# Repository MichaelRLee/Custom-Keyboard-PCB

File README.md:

# Lee Keyboard PCBs

Open source, hot-swappable board PCBs designed to be controlled by commonly available microcontroller boards (Pro Micro for the numpad, and Teensy LC, 3.2, etc. for the TKL).  These could easily be swapped out for any other board, but the qmk firmware would need to be modified for the specific controller.

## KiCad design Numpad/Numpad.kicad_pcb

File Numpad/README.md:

# leepad

<table>
<th colspan=2 style="text-align:center">Firmware</th>
<tr>
<td><a href="https://github.com/MichaelRLee/qmk_firmware/tree/numpad/keyboards/finz/leepad">QMK</a></td>
<td><a href="https://github.com/MichaelRLee/vial-qmk/tree/numpad/keyboards/finz/leepad">Vial</a></td>
</tr>
</table>

A hotswappable numpad with extra macro keys.  Designed with the intention of using a Pro Micro as the controller, though the the spacing between the two PTH collumns do not reflect this.  What that means is that wires will have to be used in place of at least one row of pin headers.  The rational for this is to allow flexibility when mounting the Pro Micro (left or right side, or relocate the Pro Micro entirely).

Files (kicad and gerber) for a mounting plate are also included, which can easily be manufactured at the same time as the PCB.  For reference, the spacing between the macro keys and the rest of the keybaord is 0.25u, and all stabalizers have the wires facing inwards.

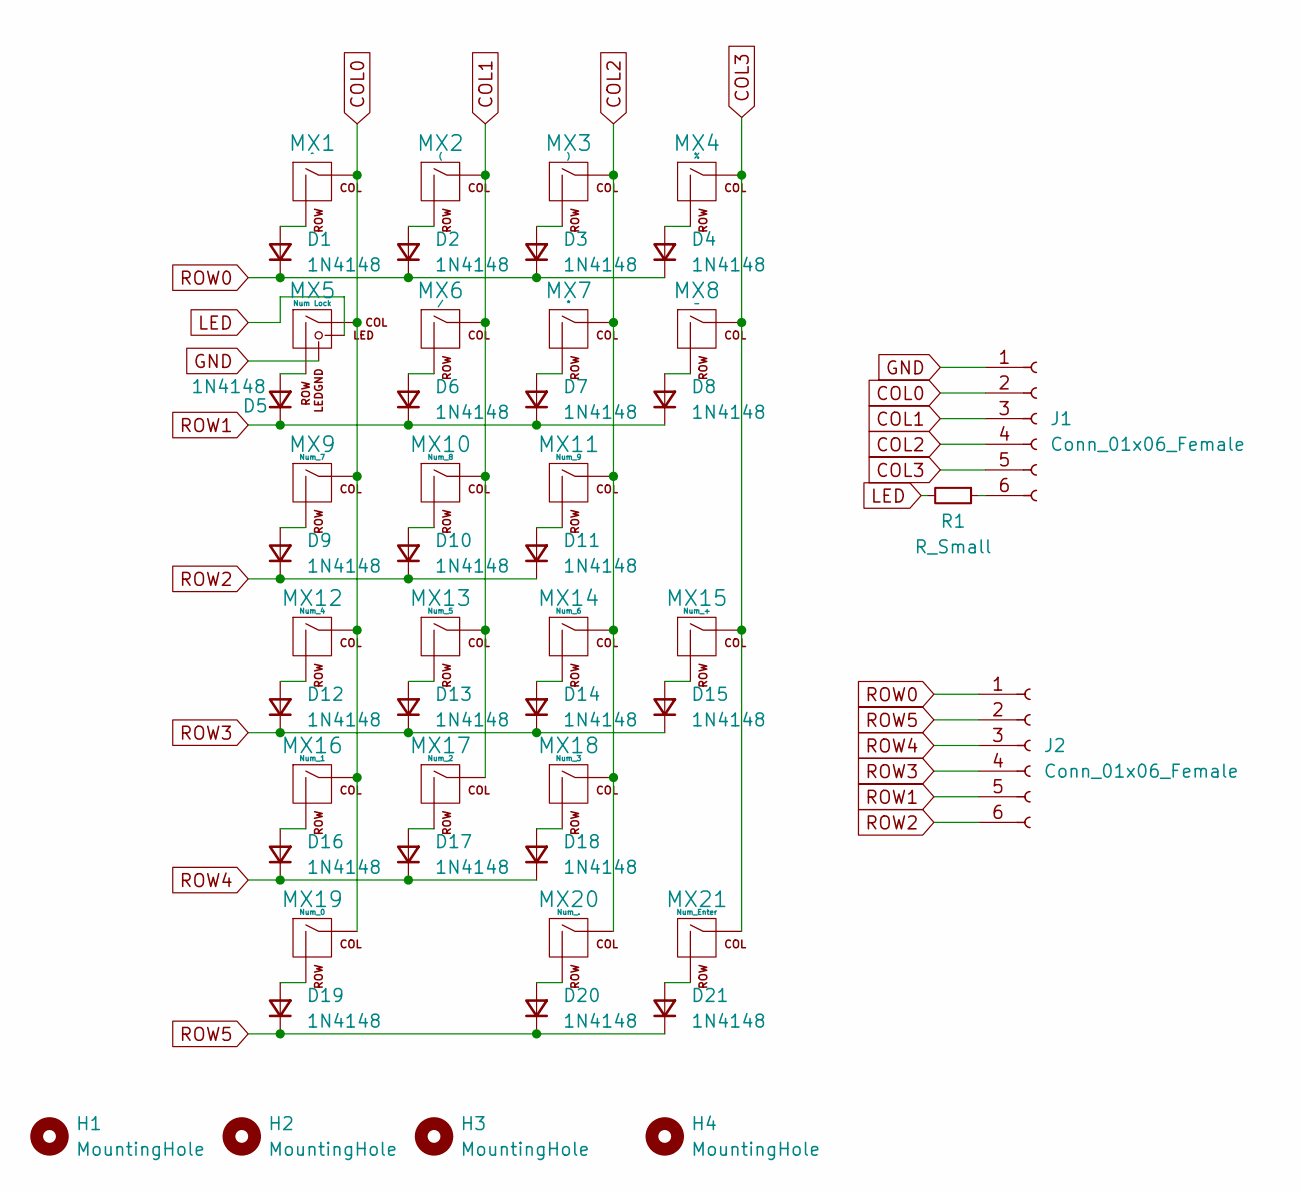
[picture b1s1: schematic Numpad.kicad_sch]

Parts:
D1, D2, D3, D4, D5, D6, D7, D8, D9, D10, D11, D12, D13, D14, D15, D16, D17, D18, D19, D20, D21: 1N4148; D_DO-34_SOD68_P7.62mm_Horizontal
H1, H2, H3, H4: MountingHole; MountingHole_2.2mm_M2_Pad
J1, J2: Conn_01x06_Female; PinHeader_1x06_P2.54mm_Vertical
MX1: ^; MXOnly-1U-Hotswap-Antishear
MX2: (; MXOnly-1U-Hotswap-Antishear
MX3: ); MXOnly-1U-Hotswap-Antishear
MX4: %; MXOnly-1U-Hotswap-Antishear
MX5: Num Lock; MXOnly-1U-Hotswap-Antishear-LED
MX6: /; MXOnly-1U-Hotswap-Antishear
MX7: *; MXOnly-1U-Hotswap-Antishear
MX8: -; MXOnly-1U-Hotswap-Antishear
MX9: Num_7; MXOnly-1U-Hotswap-Antishear
MX10: Num_8; MXOnly-1U-Hotswap-Antishear
MX11: Num_9; MXOnly-1U-Hotswap-Antishear
MX12: Num_4; MXOnly-1U-Hotswap-Antishear
MX13: Num_5; MXOnly-1U-Hotswap-Antishear
MX14: Num_6; MXOnly-1U-Hotswap-Antishear
MX15: Num_+; MXOnly-2U-Hotswap-Antishear-ReversedVerticalStabilizers
MX16: Num_1; MXOnly-1U-Hotswap-Antishear
MX17: Num_2; MXOnly-1U-Hotswap-Antishear
MX18: Num_3; MXOnly-1U-Hotswap-Antishear
MX19: Num_0; MXOnly-2U-Hotswap-Antishear-ReversedStabilizers
MX20: Num_.; MXOnly-1U-Hotswap-Antishear
MX21: Num_Enter; MXOnly-2U-Hotswap-Antishear-ReversedVerticalStabilizers
R1: R_Small; R_Axial_DIN0207_L6.3mm_D2.5mm_P10.16mm_Horizontal

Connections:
COL0: J1.2, MX1.1 (COL), MX5.1 (COL), MX9.1 (COL), MX12.1 (COL), MX16.1 (COL), MX19.1 (COL)
COL1: J1.3, MX2.1 (COL), MX6.1 (COL), MX10.1 (COL), MX13.1 (COL), MX17.1 (COL)
COL2: J1.4, MX3.1 (COL), MX7.1 (COL), MX11.1 (COL), MX14.1 (COL), MX18.1 (COL), MX20.1 (COL)
COL3: J1.5, MX4.1 (COL), MX8.1 (COL), MX15.1 (COL), MX21.1 (COL)
GND: J1.1, MX5.4 (LEDGND)
LED: MX5.3 (LED), R1.2
unnamed: D1.2 (A), MX1.2 (ROW)
unnamed: D2.2 (A), MX2.2 (ROW)
unnamed: D3.2 (A), MX3.2 (ROW)
unnamed: D4.2 (A), MX4.2 (ROW)
unnamed: D5.2 (A), MX5.2 (ROW)
unnamed: D6.2 (A), MX6.2 (ROW)
unnamed: D7.2 (A), MX7.2 (ROW)
unnamed: D8.2 (A), MX8.2 (ROW)
unnamed: D9.2 (A), MX9.2 (ROW)
unnamed: D10.2 (A), MX10.2 (ROW)
unnamed: D11.2 (A), MX11.2 (ROW)
unnamed: D12.2 (A), MX12.2 (ROW)
unnamed: D13.2 (A), MX13.2 (ROW)
unnamed: D14.2 (A), MX14.2 (ROW)
unnamed: D15.2 (A), MX15.2 (ROW)
unnamed: D16.2 (A), MX16.2 (ROW)
unnamed: D17.2 (A), MX17.2 (ROW)
unnamed: D18.2 (A), MX18.2 (ROW)
unnamed: D19.2 (A), MX19.2 (ROW)
unnamed: D20.2 (A), MX20.2 (ROW)
unnamed: D21.2 (A), MX21.2 (ROW)
unnamed: J1.6, R1.1
ROW0: D1.1 (K), D2.1 (K), D3.1 (K), D4.1 (K), J2.1
ROW1: D5.1 (K), D6.1 (K), D7.1 (K), D8.1 (K), J2.5
ROW2: D9.1 (K), D10.1 (K), D11.1 (K), J2.6
ROW3: D12.1 (K), D13.1 (K), D14.1 (K), D15.1 (K), J2.4
ROW4: D16.1 (K), D17.1 (K), D18.1 (K), J2.3
ROW5: D19.1 (K), D20.1 (K), D21.1 (K), J2.2

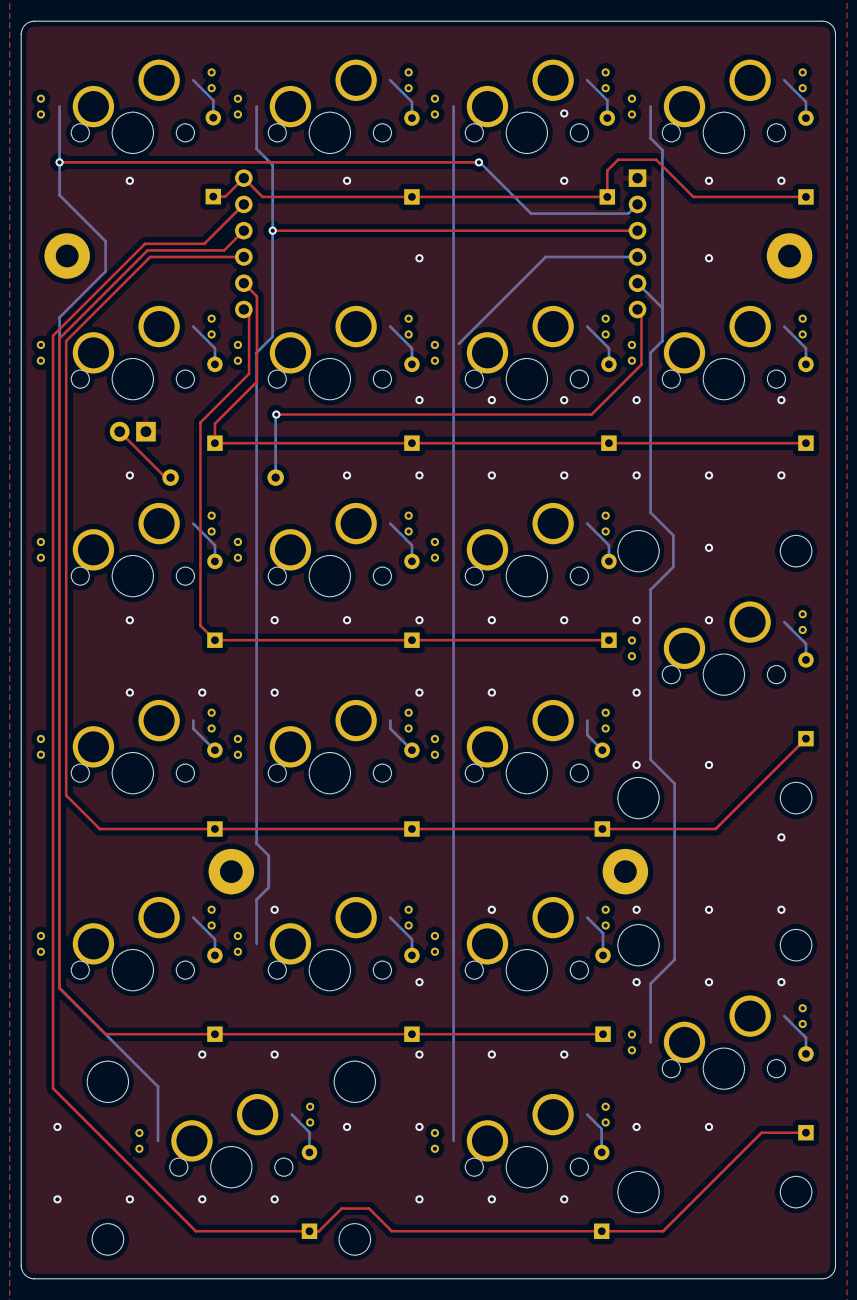
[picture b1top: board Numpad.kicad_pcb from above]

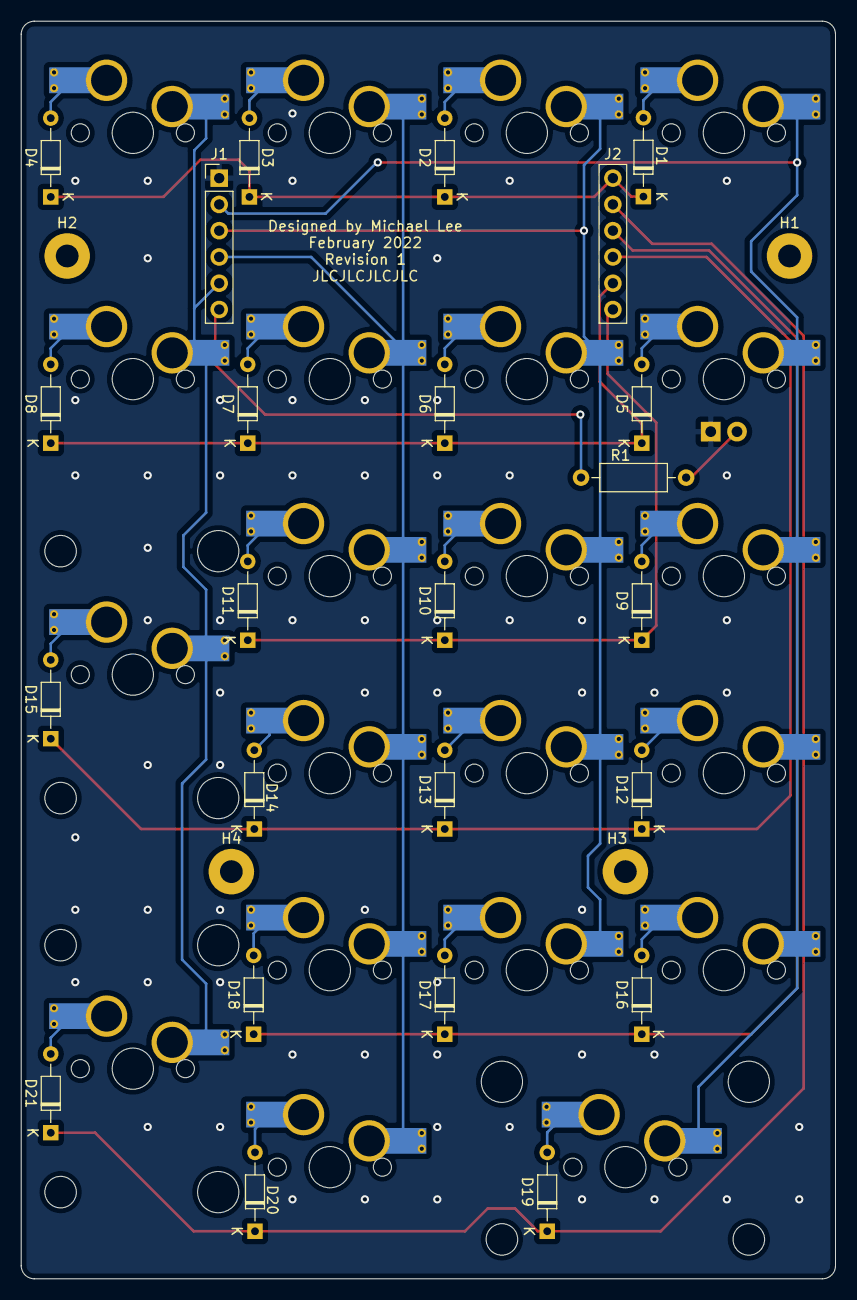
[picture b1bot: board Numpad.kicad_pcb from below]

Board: 2 copper layers, 78.7 x 121.6 mm, 49 parts (28 on the bottom side), 34 nets.

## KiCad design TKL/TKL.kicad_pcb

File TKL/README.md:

# tenleeless

<table>
<th colspan=2 style="text-align:center">Firmware</th>
<tr>
<td><a href="https://github.com/MichaelRLee/qmk_firmware/tree/tenkeyless/keyboards/finz/tenleeless">QMK</a></td>
<td><a href="">Vial</a></td>
</tr>
</table>

A hotswappable tenkeyless board, designed  with using a Teensy 3.2 as the controller.  Other controller boards with the same pinout (like the Teensy LC), should be usable, or any board with enough pins if not using pin headers (though adjustments to the QMK firmware would be needed).

### Design notes

The gap between the function keys and the alphanumeric cluster, as well as between the cluster and the nav keys, is 0.25u.  The spacebar stabalizer is the only one that has been flipped (wire north of the switch).  Any non-tray mounted mounting plate that fits the above should work with this PCB, though it was designed using a kbd8x plate as reference.

The board was is limted to a 7u space bar (1.5u ctrl/alt keys and 1u win keys, no fn/menu key), as well as a stepped caps lock.

As the microcontroller is located above the left arrow key, you may want to use a daughterboard (or female USB port).

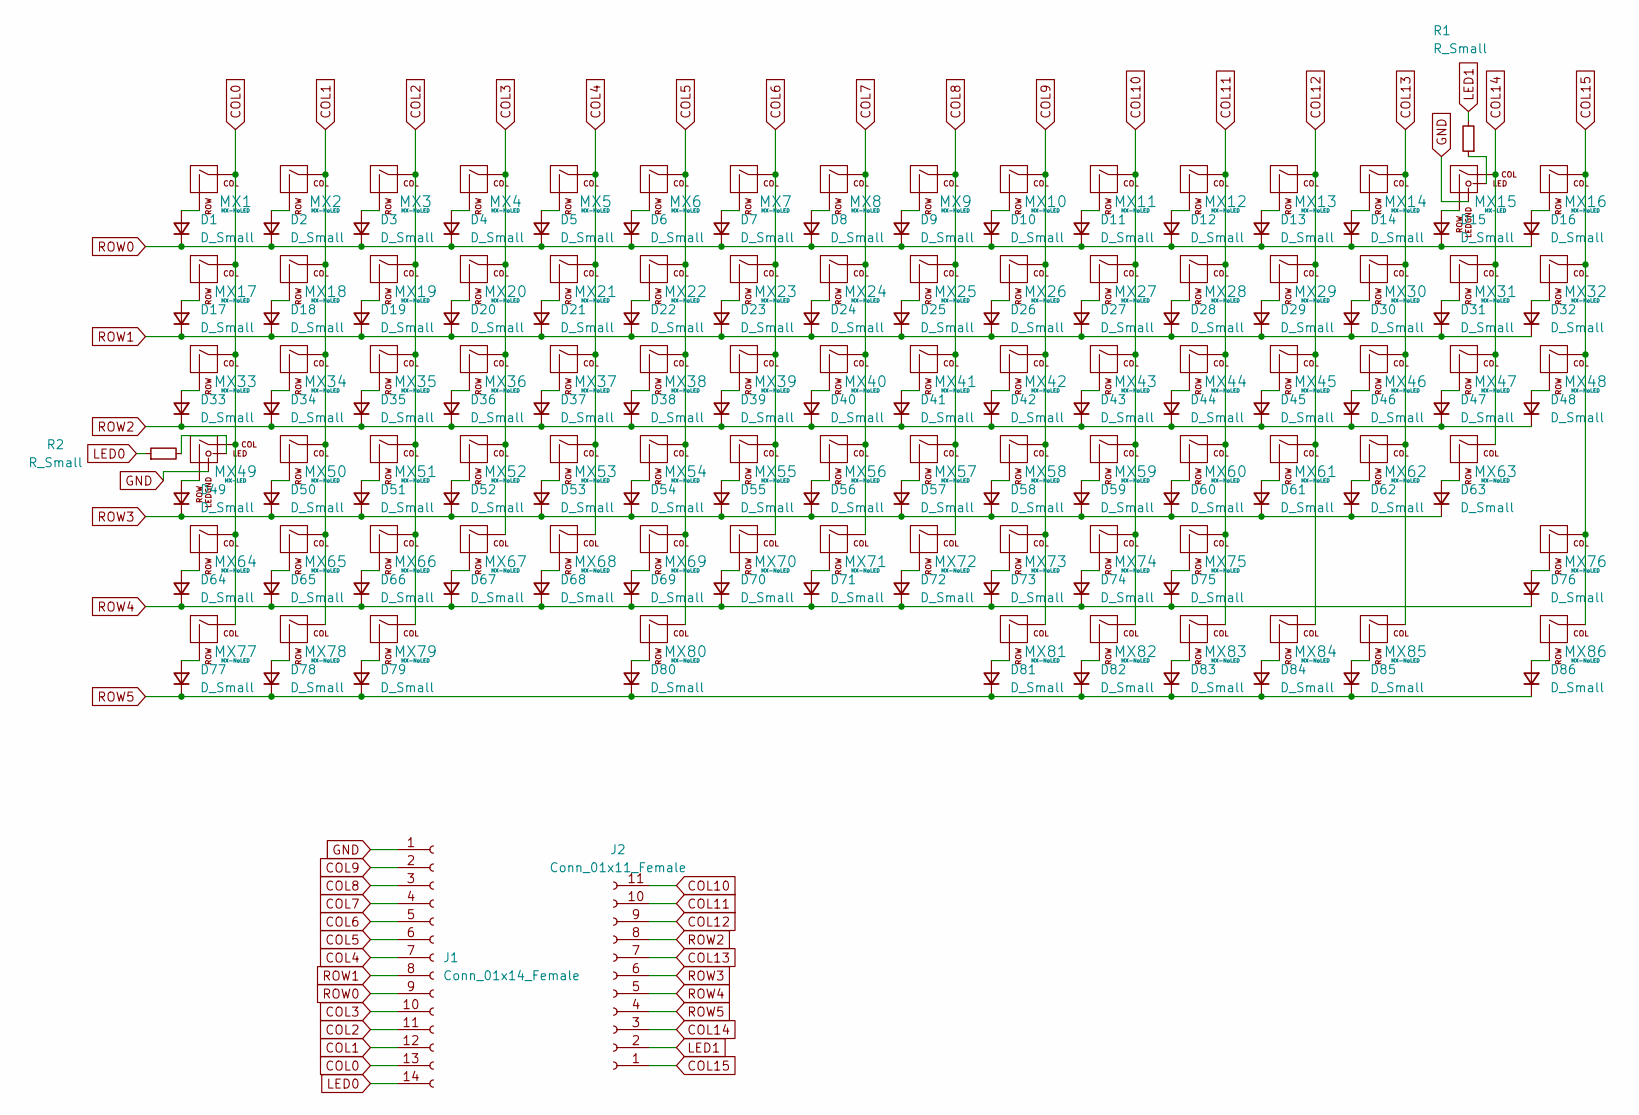
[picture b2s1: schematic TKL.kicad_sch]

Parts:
D1, D2, D3, D4, D5, D6, D7, D8, D9, D10, D11, D12, D13, D14, D15, D16, D17, D18, D19, D20, D21, D22, D23, D24, D25, D26, D27, D28, D29, D30, D31, D32, D33, D34, D35, D36, D37, D38, D39, D40, D41, D42, D43, D44, D45, D46, D47, D48, D49, D50, D51, D52, D53, D54, D55, D56, D57, D58, D59, D60, D61, D62, D63, D64, D65, D66, D67, D68, D69, D70, D71, D72, D73, D74, D75, D76, D77, D78, D79, D80, D81, D82, D83, D84, D85, D86: D_Small; D_DO-35_SOD27_P7.62mm_Horizontal
J1: Conn_01x14_Female; PinHeader_1x14_P2.54mm_Vertical
J2: Conn_01x11_Female; PinHeader_1x11_P2.54mm_Vertical
MX1, MX2, MX3, MX4, MX5, MX6, MX7, MX8, MX9, MX10, MX11, MX12, MX13, MX14, MX16, MX18, MX19, MX20, MX21, MX22, MX23, MX24, MX25, MX26, MX27, MX28, MX29, MX31, MX32, MX34, MX35, MX36, MX37, MX38, MX39, MX40, MX41, MX42, MX43, MX44, MX45, MX47, MX48, MX50, MX51, MX52, MX53, MX54, MX55, MX56, MX57, MX58, MX59, MX60, MX62, MX63, MX65, MX66, MX67, MX68, MX69, MX70, MX71, MX72, MX73, MX74, MX76, MX78, MX82, MX84, MX85, MX86: MX-NoLED; MXOnly-1U-Hotswap-Antishear
MX15: MX-LED; MXOnly-1U-Hotswap-Antishear-LED
MX17: MX-NoLED; MXOnly-1U-Hotswap
MX30: MX-NoLED; MXOnly-2U-Hotswap-Antishear
MX33, MX46, MX77, MX79, MX81, MX83: MX-NoLED; MXOnly-1.5U-Hotswap-Antishear
MX49: MX-LED; MXOnly-Caps-Hotswap-Antishear-LED
MX61, MX64: MX-NoLED; MXOnly-2.25U-Hotswap-Antishear
MX75: MX-NoLED; MXOnly-2.75U-Hotswap-Antishear
MX80: MX-NoLED; MXOnly-7U-Hotswap-Antishear
R1, R2: R_Small; R_Axial_DIN0207_L6.3mm_D2.5mm_P7.62mm_Horizontal

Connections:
COL0: J1.13, MX1.1 (COL), MX17.1 (COL), MX33.1 (COL), MX49.1 (COL), MX64.1 (COL), MX77.1 (COL)
COL1: J1.12, MX2.1 (COL), MX18.1 (COL), MX34.1 (COL), MX50.1 (COL), MX65.1 (COL), MX78.1 (COL)
COL2: J1.11, MX3.1 (COL), MX19.1 (COL), MX35.1 (COL), MX51.1 (COL), MX66.1 (COL), MX79.1 (COL)
COL3: J1.10, MX4.1 (COL), MX20.1 (COL), MX36.1 (COL), MX52.1 (COL), MX67.1 (COL)
COL4: J1.7, MX5.1 (COL), MX21.1 (COL), MX37.1 (COL), MX53.1 (COL), MX68.1 (COL)
COL5: J1.6, MX6.1 (COL), MX22.1 (COL), MX38.1 (COL), MX54.1 (COL), MX69.1 (COL), MX80.1 (COL)
COL6: J1.5, MX7.1 (COL), MX23.1 (COL), MX39.1 (COL), MX55.1 (COL), MX70.1 (COL)
COL7: J1.4, MX8.1 (COL), MX24.1 (COL), MX40.1 (COL), MX56.1 (COL), MX71.1 (COL)
COL8: J1.3, MX9.1 (COL), MX25.1 (COL), MX41.1 (COL), MX57.1 (COL), MX72.1 (COL)
COL9: J1.2, MX10.1 (COL), MX26.1 (COL), MX42.1 (COL), MX58.1 (COL), MX73.1 (COL), MX81.1 (COL)
COL10: J2.11, MX11.1 (COL), MX27.1 (COL), MX43.1 (COL), MX59.1 (COL), MX74.1 (COL), MX82.1 (COL)
COL11: J2.10, MX12.1 (COL), MX28.1 (COL), MX44.1 (COL), MX60.1 (COL), MX75.1 (COL), MX83.1 (COL)
COL12: J2.9, MX13.1 (COL), MX29.1 (COL), MX45.1 (COL), MX61.1 (COL), MX84.1 (COL)
COL13: J2.7, MX14.1 (COL), MX30.1 (COL), MX46.1 (COL), MX62.1 (COL), MX85.1 (COL)
COL14: J2.3, MX15.1 (COL), MX31.1 (COL), MX47.1 (COL), MX63.1 (COL)
COL15: J2.1, MX16.1 (COL), MX32.1 (COL), MX48.1 (COL), MX76.1 (COL), MX86.1 (COL)
GND: J1.1, MX15.4 (LEDGND), MX49.4 (LEDGND)
LED0: J1.14, R2.1
LED1: J2.2, R1.2
unnamed: D1.2 (A), MX1.2 (ROW)
unnamed: D2.2 (A), MX2.2 (ROW)
unnamed: D3.2 (A), MX3.2 (ROW)
unnamed: D4.2 (A), MX4.2 (ROW)
unnamed: D5.2 (A), MX5.2 (ROW)
unnamed: D6.2 (A), MX6.2 (ROW)
unnamed: D7.2 (A), MX7.2 (ROW)
unnamed: D8.2 (A), MX8.2 (ROW)
unnamed: D9.2 (A), MX9.2 (ROW)
unnamed: D10.2 (A), MX10.2 (ROW)
unnamed: D11.2 (A), MX11.2 (ROW)
unnamed: D12.2 (A), MX12.2 (ROW)
unnamed: D13.2 (A), MX13.2 (ROW)
unnamed: D14.2 (A), MX14.2 (ROW)
unnamed: D15.2 (A), MX15.2 (ROW)
unnamed: D16.2 (A), MX16.2 (ROW)
unnamed: D17.2 (A), MX17.2 (ROW)
unnamed: D18.2 (A), MX18.2 (ROW)
unnamed: D19.2 (A), MX19.2 (ROW)
unnamed: D20.2 (A), MX20.2 (ROW)
unnamed: D21.2 (A), MX21.2 (ROW)
unnamed: D22.2 (A), MX22.2 (ROW)
unnamed: D23.2 (A), MX23.2 (ROW)
unnamed: D24.2 (A), MX24.2 (ROW)
unnamed: D25.2 (A), MX25.2 (ROW)
unnamed: D26.2 (A), MX26.2 (ROW)
unnamed: D27.2 (A), MX27.2 (ROW)
unnamed: D28.2 (A), MX28.2 (ROW)
unnamed: D29.2 (A), MX29.2 (ROW)
unnamed: D30.2 (A), MX30.2 (ROW)
unnamed: D31.2 (A), MX31.2 (ROW)
unnamed: D32.2 (A), MX32.2 (ROW)
unnamed: D33.2 (A), MX33.2 (ROW)
unnamed: D34.2 (A), MX34.2 (ROW)
unnamed: D35.2 (A), MX35.2 (ROW)
unnamed: D36.2 (A), MX36.2 (ROW)
unnamed: D37.2 (A), MX37.2 (ROW)
unnamed: D38.2 (A), MX38.2 (ROW)
unnamed: D39.2 (A), MX39.2 (ROW)
unnamed: D40.2 (A), MX40.2 (ROW)
unnamed: D41.2 (A), MX41.2 (ROW)
unnamed: D42.2 (A), MX42.2 (ROW)
unnamed: D43.2 (A), MX43.2 (ROW)
unnamed: D44.2 (A), MX44.2 (ROW)
unnamed: D45.2 (A), MX45.2 (ROW)
unnamed: D46.2 (A), MX46.2 (ROW)
unnamed: D47.2 (A), MX47.2 (ROW)
unnamed: D48.2 (A), MX48.2 (ROW)
unnamed: D49.2 (A), MX49.2 (ROW)
unnamed: D50.2 (A), MX50.2 (ROW)
unnamed: D51.2 (A), MX51.2 (ROW)
unnamed: D52.2 (A), MX52.2 (ROW)
unnamed: D53.2 (A), MX53.2 (ROW)
unnamed: D54.2 (A), MX54.2 (ROW)
unnamed: D55.2 (A), MX55.2 (ROW)
unnamed: D56.2 (A), MX56.2 (ROW)
unnamed: D57.2 (A), MX57.2 (ROW)
unnamed: D58.2 (A), MX58.2 (ROW)
unnamed: D59.2 (A), MX59.2 (ROW)
unnamed: D60.2 (A), MX60.2 (ROW)
unnamed: D61.2 (A), MX61.2 (ROW)
unnamed: D62.2 (A), MX62.2 (ROW)
unnamed: D63.2 (A), MX63.2 (ROW)
unnamed: D64.2 (A), MX64.2 (ROW)
unnamed: D65.2 (A), MX65.2 (ROW)
unnamed: D66.2 (A), MX66.2 (ROW)
unnamed: D67.2 (A), MX67.2 (ROW)
unnamed: D68.2 (A), MX68.2 (ROW)
unnamed: D69.2 (A), MX69.2 (ROW)
unnamed: D70.2 (A), MX70.2 (ROW)
unnamed: D71.2 (A), MX71.2 (ROW)
unnamed: D72.2 (A), MX72.2 (ROW)
unnamed: D73.2 (A), MX73.2 (ROW)
unnamed: D74.2 (A), MX74.2 (ROW)
unnamed: D75.2 (A), MX75.2 (ROW)
unnamed: D76.2 (A), MX76.2 (ROW)
unnamed: D77.2 (A), MX77.2 (ROW)
unnamed: D78.2 (A), MX78.2 (ROW)
unnamed: D79.2 (A), MX79.2 (ROW)
unnamed: D80.2 (A), MX80.2 (ROW)
unnamed: D81.2 (A), MX81.2 (ROW)
unnamed: D82.2 (A), MX82.2 (ROW)
unnamed: D83.2 (A), MX83.2 (ROW)
unnamed: D84.2 (A), MX84.2 (ROW)
unnamed: D85.2 (A), MX85.2 (ROW)
unnamed: D86.2 (A), MX86.2 (ROW)
unnamed: MX15.3 (LED), R1.1
unnamed: MX49.3 (LED), R2.2
ROW0: D1.1 (K), D2.1 (K), D3.1 (K), D4.1 (K), D5.1 (K), D6.1 (K), D7.1 (K), D8.1 (K), D9.1 (K), D10.1 (K), D11.1 (K), D12.1 (K), D13.1 (K), D14.1 (K), D15.1 (K), D16.1 (K), J1.9
ROW1: D17.1 (K), D18.1 (K), D19.1 (K), D20.1 (K), D21.1 (K), D22.1 (K), D23.1 (K), D24.1 (K), D25.1 (K), D26.1 (K), D27.1 (K), D28.1 (K), D29.1 (K), D30.1 (K), D31.1 (K), D32.1 (K), J1.8
ROW2: D33.1 (K), D34.1 (K), D35.1 (K), D36.1 (K), D37.1 (K), D38.1 (K), D39.1 (K), D40.1 (K), D41.1 (K), D42.1 (K), D43.1 (K), D44.1 (K), D45.1 (K), D46.1 (K), D47.1 (K), D48.1 (K), J2.8
ROW3: D49.1 (K), D50.1 (K), D51.1 (K), D52.1 (K), D53.1 (K), D54.1 (K), D55.1 (K), D56.1 (K), D57.1 (K), D58.1 (K), D59.1 (K), D60.1 (K), D61.1 (K), D62.1 (K), D63.1 (K), J2.6
ROW4: D64.1 (K), D65.1 (K), D66.1 (K), D67.1 (K), D68.1 (K), D69.1 (K), D70.1 (K), D71.1 (K), D72.1 (K), D73.1 (K), D74.1 (K), D75.1 (K), D76.1 (K), J2.5
ROW5: D77.1 (K), D78.1 (K), D79.1 (K), D80.1 (K), D81.1 (K), D82.1 (K), D83.1 (K), D84.1 (K), D85.1 (K), D86.1 (K), J2.4

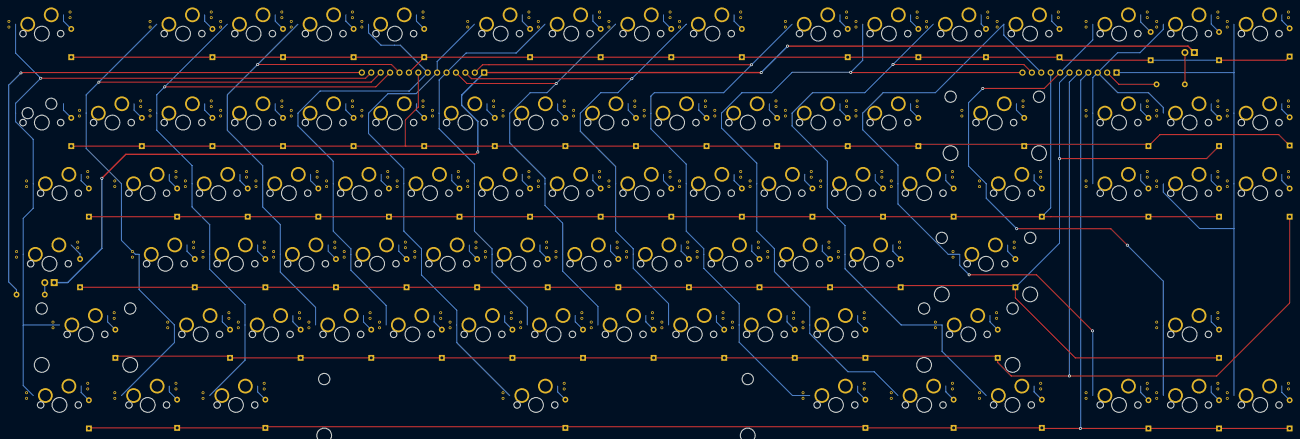
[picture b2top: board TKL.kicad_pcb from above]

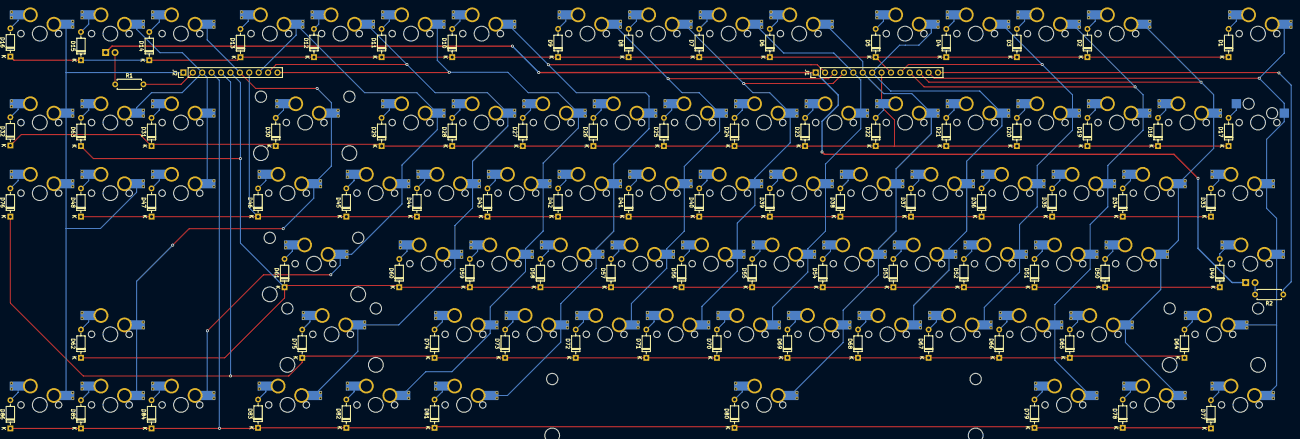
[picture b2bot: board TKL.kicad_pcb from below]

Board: 2 copper layers, 176 parts (90 on the bottom side), 113 nets.

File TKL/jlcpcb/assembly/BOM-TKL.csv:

Comment,Designator,Footprint,LCSC
Tab,MX33,MXOnly-1.5U-Hotswap-Antishear,
;,MX59,MXOnly-1U-Hotswap-Antishear,
R_Alt,MX81,MXOnly-1.5U-Hotswap-Antishear,
v,MX68,MXOnly-1U-Hotswap-Antishear,
Insert,MX31,MXOnly-1U-Hotswap-Antishear,
m,MX71,MXOnly-1U-Hotswap-Antishear,
F10,MX11,MXOnly-1U-Hotswap-Antishear,
Page Down,MX76,MXOnly-1U-Hotswap-Antishear,
F5,MX6,MXOnly-1U-Hotswap-Antishear,
Enter,MX61,MXOnly-2.25U-Hotswap-Antishear,
r,MX37,MXOnly-1U-Hotswap-Antishear,
x,MX66,MXOnly-1U-Hotswap-Antishear,
",",MX72,MXOnly-1U-Hotswap-Antishear,
L_Alt,MX79,MXOnly-1.5U-Hotswap-Antishear,
9,MX26,MXOnly-1U-Hotswap-Antishear,
5,MX22,MXOnly-1U-Hotswap-Antishear,
L_Shift,MX64,MXOnly-2.25U-Hotswap-Antishear,
-,MX28,MXOnly-1U-Hotswap-Antishear,
0,MX27,MXOnly-1U-Hotswap-Antishear,
=,MX29,MXOnly-1U-Hotswap-Antishear,
z,MX65,MXOnly-1U-Hotswap-Antishear,
g,MX54,MXOnly-1U-Hotswap-Antishear,
o,MX42,MXOnly-1U-Hotswap-Antishear,
Pause,MX16,MXOnly-1U-Hotswap-Antishear,
F4,MX5,MXOnly-1U-Hotswap-Antishear,
7,MX24,MXOnly-1U-Hotswap-Antishear,
j,MX56,MXOnly-1U-Hotswap-Antishear,
F11,MX12,MXOnly-1U-Hotswap-Antishear,
Backspace,MX30,MXOnly-2U-Hotswap-Antishear,
h,MX55,MXOnly-1U-Hotswap-Antishear,
.,MX73,MXOnly-1U-Hotswap-Antishear,
End,MX48,MXOnly-1U-Hotswap-Antishear,
Print Screen,MX14,MXOnly-1U-Hotswap-Antishear,
q,MX34,MXOnly-1U-Hotswap-Antishear,
3,MX20,MXOnly-1U-Hotswap-Antishear,
p,MX43,MXOnly-1U-Hotswap-Antishear,
c,MX67,MXOnly-1U-Hotswap-Antishear,
n,MX70,MXOnly-1U-Hotswap-Antishear,
F8,MX9,MXOnly-1U-Hotswap-Antishear,
],MX45,MXOnly-1U-Hotswap-Antishear,
Page Up,MX32,MXOnly-1U-Hotswap-Antishear,
y,MX39,MXOnly-1U-Hotswap-Antishear,
F2,MX3,MXOnly-1U-Hotswap-Antishear,
i,MX41,MXOnly-1U-Hotswap-Antishear,
a,MX50,MXOnly-1U-Hotswap-Antishear,
F1,MX2,MXOnly-1U-Hotswap-Antishear,
\,MX46,MXOnly-1.5U-Hotswap-Antishear,
Teensy3.2,U1,Teensy30_31_32_LC,
L_Ctrl,MX77,MXOnly-1.5U-Hotswap-Antishear,
2,MX19,MXOnly-1U-Hotswap-Antishear,
L_Win,MX78,MXOnly-1U-Hotswap-Antishear,
Scroll Lock,MX15,MXOnly-1U-Hotswap-Antishear-LED,
[,MX44,MXOnly-1U-Hotswap-Antishear,
R_Shift,MX75,MXOnly-2.75U-Hotswap-Antishear,
Down,MX85,MXOnly-1U-Hotswap-Antishear,
F6,MX7,MXOnly-1U-Hotswap-Antishear,
',MX60,MXOnly-1U-Hotswap-Antishear,
u,MX40,MXOnly-1U-Hotswap-Antishear,
Left,MX84,MXOnly-1U-Hotswap-Antishear,
4,MX21,MXOnly-1U-Hotswap-Antishear,
Space,MX80,MXOnly-7U-Hotswap-Antishear-ReversedStabilizers,
Caps Lock,MX49,MXOnly-1U-Hotswap-Antishear-LED,
F3,MX4,MXOnly-1U-Hotswap-Antishear,
Esc,MX1,MXOnly-1U-Hotswap-Antishear,
6,MX23,MXOnly-1U-Hotswap-Antishear,
F12,MX13,MXOnly-1U-Hotswap-Antishear,
t,MX38,MXOnly-1U-Hotswap-Antishear,
Home,MX63,MXOnly-1U-Hotswap-Antishear,
R_Ctrl,MX83,MXOnly-1.5U-Hotswap-Antishear,
F7,MX8,MXOnly-1U-Hotswap-Antishear,
Delete,MX47,MXOnly-1U-Hotswap-Antishear,
k,MX57,MXOnly-1U-Hotswap-Antishear,
R_Win,MX82,MXOnly-1U-Hotswap-Antishear,
F9,MX10,MXOnly-1U-Hotswap-Antishear,
Up,MX62,MXOnly-1U-Hotswap-Antishear,
e,MX36,MXOnly-1U-Hotswap-Antishear,
d,MX52,MXOnly-1U-Hotswap-Antishear,
8,MX25,MXOnly-1U-Hotswap-Antishear,
w,MX35,MXOnly-1U-Hotswap-Antishear,
`,MX17,MXOnly-1U-Hotswap-Antishear,
b,MX69,MXOnly-1U-Hotswap-Antishear,
Right,MX86,MXOnly-1U-Hotswap-Antishear,
/,MX74,MXOnly-1U-Hotswap-Antishear,
1,MX18,MXOnly-1U-Hotswap-Antishear,
l,MX58,MXOnly-1U-Hotswap-Antishear,
s,MX51,MXOnly-1U-Hotswap-Antishear,
f,MX53,MXOnly-1U-Hotswap-Antishear,
1N4148,D39,D_DO-35_SOD27_P7.62mm_Horizontal,
1N4148,D36,D_DO-35_SOD27_P7.62mm_Horizontal,
1N4148,D24,D_DO-35_SOD27_P7.62mm_Horizontal,
1N4148,D73,D_DO-35_SOD27_P7.62mm_Horizontal,
1N4148,D41,D_DO-35_SOD27_P7.62mm_Horizontal,
1N4148,D7,D_DO-35_SOD27_P7.62mm_Horizontal,
1N4148,D28,D_DO-35_SOD27_P7.62mm_Horizontal,
1N4148,D57,D_DO-35_SOD27_P7.62mm_Horizontal,
1N4148,D21,D_DO-35_SOD27_P7.62mm_Horizontal,
1N4148,D75,D_DO-35_SOD27_P7.62mm_Horizontal,
1N4148,D72,D_DO-35_SOD27_P7.62mm_Horizontal,
1N4148,D37,D_DO-35_SOD27_P7.62mm_Horizontal,
1N4148,D60,D_DO-35_SOD27_P7.62mm_Horizontal,
1N4148,D27,D_DO-35_SOD27_P7.62mm_Horizontal,
1N4148,D77,D_DO-35_SOD27_P7.62mm_Horizontal,
1N4148,D5,D_DO-35_SOD27_P7.62mm_Horizontal,
1N4148,D46,D_DO-35_SOD27_P7.62mm_Horizontal,
1N4148,D86,D_DO-35_SOD27_P7.62mm_Horizontal,
1N4148,D64,D_DO-35_SOD27_P7.62mm_Horizontal,
1N4148,D44,D_DO-35_SOD27_P7.62mm_Horizontal,
1N4148,D59,D_DO-35_SOD27_P7.62mm_Horizontal,
1N4148,D1,D_DO-35_SOD27_P7.62mm_Horizontal,
1N4148,D30,D_DO-35_SOD27_P7.62mm_Horizontal,
1N4148,D61,D_DO-35_SOD27_P7.62mm_Horizontal,
1N4148,D19,D_DO-35_SOD27_P7.62mm_Horizontal,
1N4148,D25,D_DO-35_SOD27_P7.62mm_Horizontal,
1N4148,D3,D_DO-35_SOD27_P7.62mm_Horizontal,
1N4148,D49,D_DO-35_SOD27_P7.62mm_Horizontal,
1N4148,D81,D_DO-35_SOD27_P7.62mm_Horizontal,
1N4148,D14,D_DO-35_SOD27_P7.62mm_Horizontal,
1N4148,D63,D_DO-35_SOD27_P7.62mm_Horizontal,
1N4148,D78,D_DO-35_SOD27_P7.62mm_Horizontal,
1N4148,D9,D_DO-35_SOD27_P7.62mm_Horizontal,
1N4148,D79,D_DO-35_SOD27_P7.62mm_Horizontal,
1N4148,D12,D_DO-35_SOD27_P7.62mm_Horizontal,
1N4148,D43,D_DO-35_SOD27_P7.62mm_Horizontal,
1N4148,D82,D_DO-35_SOD27_P7.62mm_Horizontal,
1N4148,D48,D_DO-35_SOD27_P7.62mm_Horizontal,
1N4148,D53,D_DO-35_SOD27_P7.62mm_Horizontal,
1N4148,D40,D_DO-35_SOD27_P7.62mm_Horizontal,
1N4148,D31,D_DO-35_SOD27_P7.62mm_Horizontal,
1N4148,D35,D_DO-35_SOD27_P7.62mm_Horizontal,
1N4148,D45,D_DO-35_SOD27_P7.62mm_Horizontal,
1N4148,D68,D_DO-35_SOD27_P7.62mm_Horizontal,
1N4148,D29,D_DO-35_SOD27_P7.62mm_Horizontal,
1N4148,D54,D_DO-35_SOD27_P7.62mm_Horizontal,
1N4148,D65,D_DO-35_SOD27_P7.62mm_Horizontal,
1N4148,D33,D_DO-35_SOD27_P7.62mm_Horizontal,
1N4148,D51,D_DO-35_SOD27_P7.62mm_Horizontal,
1N4148,D70,D_DO-35_SOD27_P7.62mm_Horizontal,
1N4148,D11,D_DO-35_SOD27_P7.62mm_Horizontal,
1N4148,D6,D_DO-35_SOD27_P7.62mm_Horizontal,
1N4148,D69,D_DO-35_SOD27_P7.62mm_Horizontal,
1N4148,D52,D_DO-35_SOD27_P7.62mm_Horizontal,
1N4148,D67,D_DO-35_SOD27_P7.62mm_Horizontal,
1N4148,D32,D_DO-35_SOD27_P7.62mm_Horizontal,
1N4148,D18,D_DO-35_SOD27_P7.62mm_Horizontal,
1N4148,D34,D_DO-35_SOD27_P7.62mm_Horizontal,
1N4148,D47,D_DO-35_SOD27_P7.62mm_Horizontal,
1N4148,D62,D_DO-35_SOD27_P7.62mm_Horizontal,
1N4148,D16,D_DO-35_SOD27_P7.62mm_Horizontal,
1N4148,D85,D_DO-35_SOD27_P7.62mm_Horizontal,
1N4148,D15,D_DO-35_SOD27_P7.62mm_Horizontal,
1N4148,D20,D_DO-35_SOD27_P7.62mm_Horizontal,
1N4148,D83,D_DO-35_SOD27_P7.62mm_Horizontal,
1N4148,D10,D_DO-35_SOD27_P7.62mm_Horizontal,
1N4148,D76,D_DO-35_SOD27_P7.62mm_Horizontal,
1N4148,D50,D_DO-35_SOD27_P7.62mm_Horizontal,
R_Small,R1,R_Axial_DIN0207_L6.3mm_D2.5mm_P7.62mm_Horizontal,
1N4148,D58,D_DO-35_SOD27_P7.62mm_Horizontal,
1N4148,D13,D_DO-35_SOD27_P7.62mm_Horizontal,
1N4148,D80,D_DO-35_SOD27_P7.62mm_Horizontal,
1N4148,D4,D_DO-35_SOD27_P7.62mm_Horizontal,
1N4148,D8,D_DO-35_SOD27_P7.62mm_Horizontal,
1N4148,D55,D_DO-35_SOD27_P7.62mm_Horizontal,
1N4148,D38,D_DO-35_SOD27_P7.62mm_Horizontal,
1N4148,D56,D_DO-35_SOD27_P7.62mm_Horizontal,
1N4148,D42,D_DO-35_SOD27_P7.62mm_Horizontal,
1N4148,D2,D_DO-35_SOD27_P7.62mm_Horizontal,
1N4148,D74,D_DO-35_SOD27_P7.62mm_Horizontal,
1N4148,D84,D_DO-35_SOD27_P7.62mm_Horizontal,
R_Small,R2,R_Axial_DIN0207_L6.3mm_D2.5mm_P7.62mm_Horizontal,
1N4148,D66,D_DO-35_SOD27_P7.62mm_Horizontal,
1N4148,D17,D_DO-35_SOD27_P7.62mm_Horizontal,
1N4148,D22,D_DO-35_SOD27_P7.62mm_Horizontal,
1N4148,D26,D_DO-35_SOD27_P7.62mm_Horizontal,
1N4148,D71,D_DO-35_SOD27_P7.62mm_Horizontal,
1N4148,D23,D_DO-35_SOD27_P7.62mm_Horizontal,

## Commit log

2022-01-28 Submodule libraries added, TKL project initialized
2022-01-29 TKL matrix added
2022-01-29 Submodule added for teensy. Libraries updated
2022-02-12 Reworked schematic and pcb
2022-02-12 Completed PCB and fixed spacing
2022-02-12 Added ground planes and KDB8x MKII screw holes
2022-02-12 Added Via Stitching
2022-02-14 Removed mounting holes, improved board aesthetics
2022-02-14 Added silkscreen and decoration
2022-02-14 Created numpad. Cleaned up repo
2022-02-14 Minor update
2022-02-14 Swapped header pins on numpad
2022-02-16 Set track width to 10 mils
2022-02-16 Changed traces on TKL to connect directly to teensy board
2022-02-17 Flipped orientation of Teensy and re-added via stitching
2022-02-17 Added mounting holes to numpad
2022-02-19 Reversed spacebar stab. Added jlcpcb gerber files
2022-02-20 Library paths changed to relative paths
2022-02-21 changed numpad mounting hole size to M2
2022-02-21 New number gerber files
2022-02-21 Redid PCB borders to be uniform between the numpad and tkl board
2022-02-21 Moved pins on numpad
2022-02-21 Fixed alignment of the TKL mounting plate template. Set TKL library path to be relative
2022-02-21 Added numpad mounting plate (and adjusted mounting hole locations)
2022-03-14 Updated readme and silkscreens
2022-03-14 Create LICENSE
    (cherry picked from commit 264677fbba7e0bc9fe4bfac08714a86b68879d78)
2022-03-16 Updated readmes
2022-03-17 Updated tenkeyless readme
2022-04-11 Updated pcb to fix minor interferance issue. Generated new plate as stabilizers did not fit using the old one.
